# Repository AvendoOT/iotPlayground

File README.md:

# iotPlayground
Playground for embedded stuff
Laboratory exercises, homemade projects, self-education...

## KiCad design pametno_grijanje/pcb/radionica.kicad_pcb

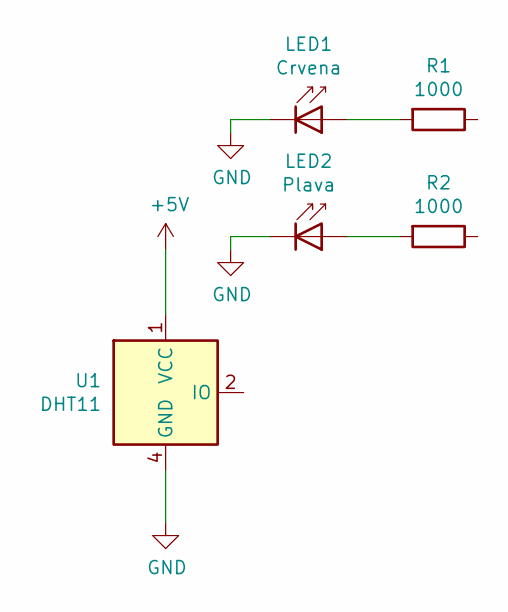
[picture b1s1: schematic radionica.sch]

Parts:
LED1: Crvena; LED_D5.0mm_IRGrey
LED2: Plava; LED_D5.0mm_IRGrey
R1, R2: 1000; R_0201_0603Metric
U1: DHT11; Aosong_DHT11_5.5x12.0_P2.54mm

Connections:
+5V: U1.1 (VCC)
GND: LED1.1 (K), LED2.1 (K), U1.4 (GND)
unnamed: LED1.2 (A), R1.2
unnamed: LED2.2 (A), R2.2

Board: 2 copper layers, 5 parts (0 on the bottom side), 3 nets, no tracks yet.

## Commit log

2021-10-10 Misc projects
2021-10-15 Added smart heating IOT app
